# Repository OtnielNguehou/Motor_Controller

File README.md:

# Motor_Controller
Designed and developed a custom PCB-based voltage multiplier circuit to generate a higher DC output voltage from a low-voltage input source. The project was motivated by the need to provide sufficient voltage for a future DC motor controller design while utilizing readily available components.

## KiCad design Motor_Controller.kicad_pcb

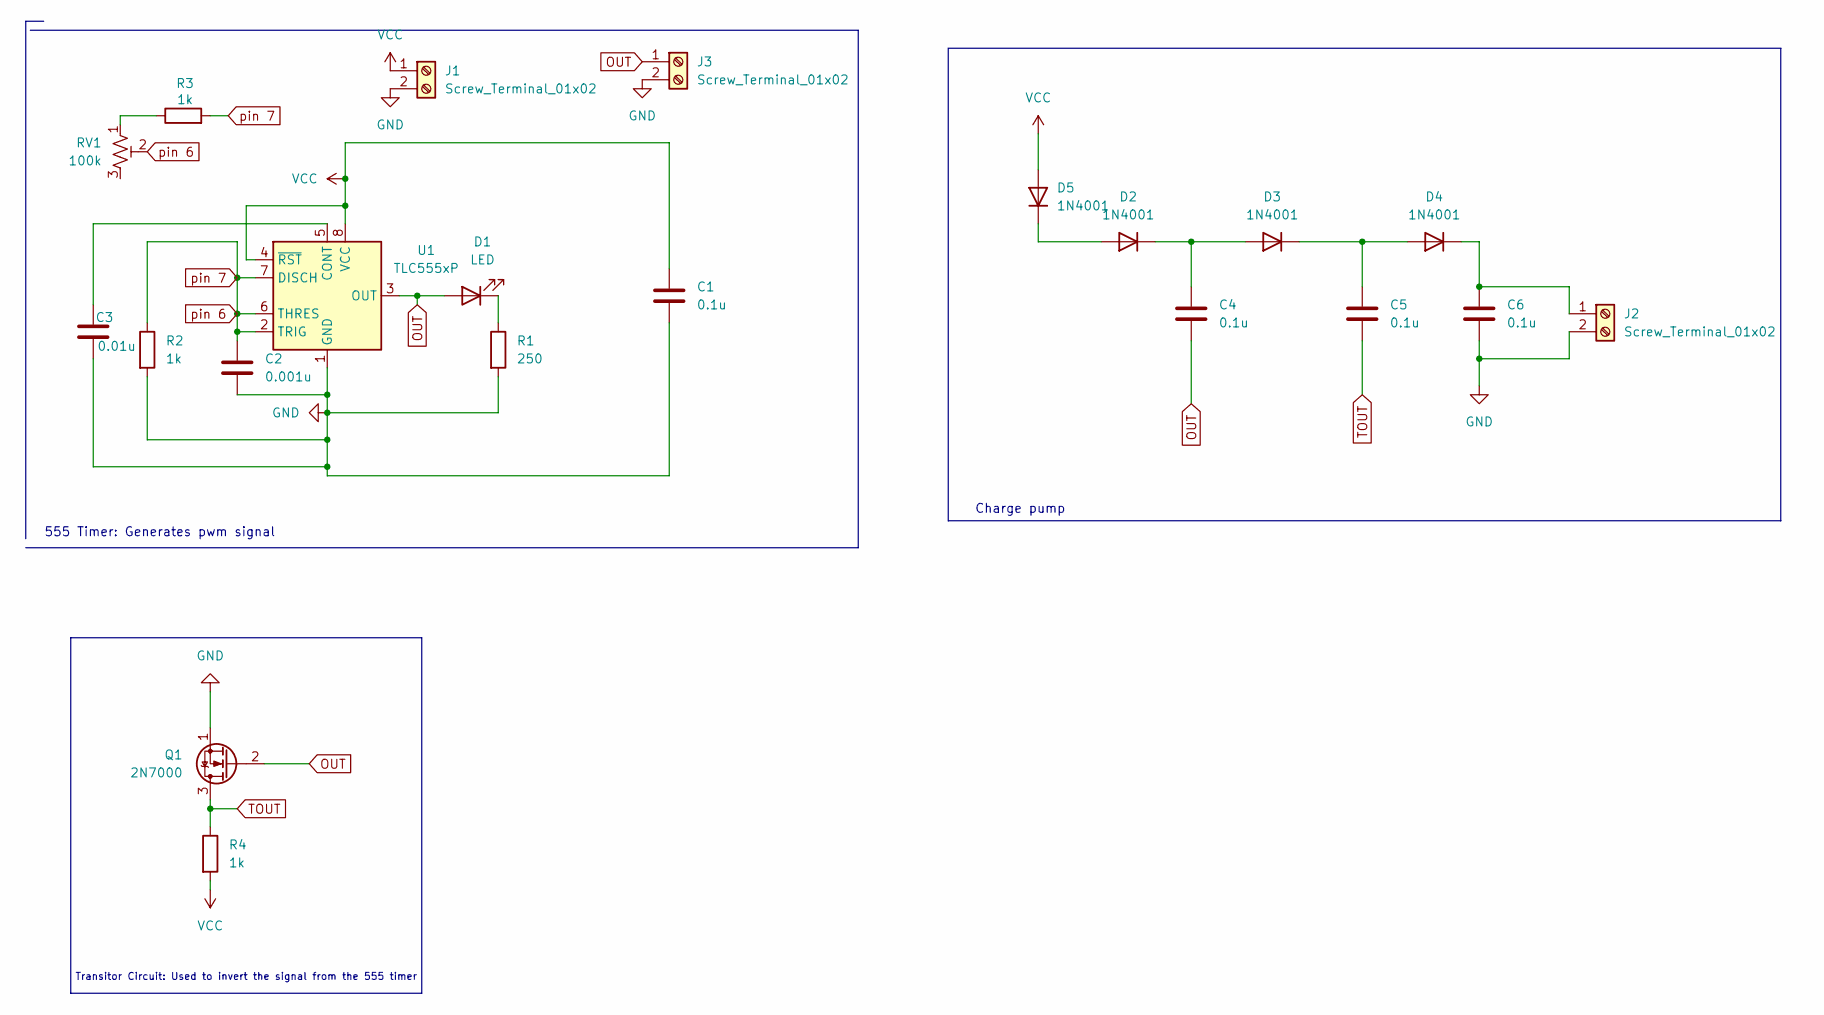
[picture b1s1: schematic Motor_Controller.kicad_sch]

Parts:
C1, C4, C5, C6: 0.1u; C_Rect_L4.6mm_W2.0mm_P2.50mm_MKS02_FKP02
C2: 0.001u; C_Rect_L4.6mm_W2.0mm_P2.50mm_MKS02_FKP02
C3: 0.01u; C_Rect_L4.6mm_W2.0mm_P2.50mm_MKS02_FKP02
D1: LED; LED_D3.0mm_Horizontal_O1.27mm_Z2.0mm
D2, D3, D4, D5: 1N4001; D_DO-41_SOD81_P10.16mm_Horizontal
J1, J2, J3: Screw_Terminal_01x02; TerminalBlock_Xinya_XY308-2.54-2P_1x02_P2.54mm_Horizontal
Q1: 2N7000; TO-92_Inline
R1: 250; R_Axial_DIN0204_L3.6mm_D1.6mm_P5.08mm_Horizontal
R2, R3, R4: 1k; R_Axial_DIN0204_L3.6mm_D1.6mm_P5.08mm_Horizontal
RV1: 100k; Potentiometer_Vishay_T93YA_Vertical
U1: TLC555xP; DIP-8_W7.62mm

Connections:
GND: C1.2, C2.2, C3.2, C6.2, J1.2, J2.2, J3.2, Q1.1 (S), R1.2, R2.2, U1.1 (GND)
unnamed: D1.1 (K), R1.1
unnamed: D2.2 (A), D5.1 (K)
unnamed: C4.1, D2.1 (K), D3.2 (A)
unnamed: C5.1, D3.1 (K), D4.2 (A)
unnamed: C6.1, D4.1 (K), J2.1
unnamed: R3.1, RV1.1
unnamed: C3.1, U1.5 (CONT)
OUT: C4.2, D1.2 (A), J3.1, Q1.2 (G), U1.3 (OUT)
TOUT: C5.2, Q1.3 (D), R4.1
VCC: C1.1, D5.2 (A), J1.1, R4.2, U1.4 (~RST), U1.8 (VCC)
pin 6: C2.1, R2.1, R3.2, RV1.2, U1.2 (TRIG), U1.6 (THRES), U1.7 (DISCH)

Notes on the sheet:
Charge pump
Transitor Circuit: Used to invert the signal from the 555 timer
555 Timer: Generates pwm signal

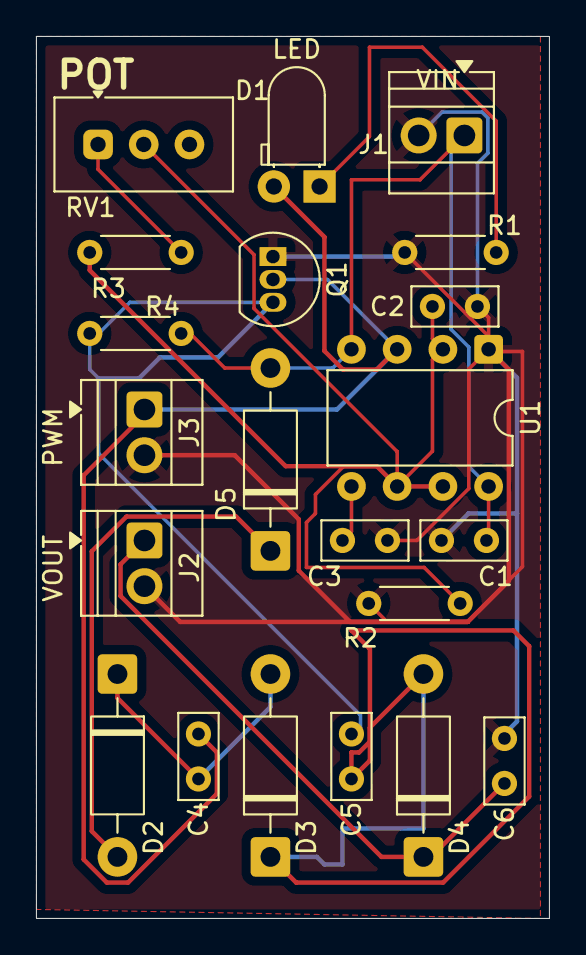
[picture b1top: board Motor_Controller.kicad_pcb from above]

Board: 2 copper layers, 28.5 x 49.0 mm, 21 parts (0 on the bottom side), 12 nets.

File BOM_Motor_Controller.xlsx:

Reference | Qty | Value | DNP | Exclude from BOM | Exclude from Board | Footprint | Datasheet
C1,C4 | 2 | 0.1u |  |  |  | Capacitor_THT:C_Rect_L4.6mm_W2.0mm_P2.50mm_MKS02_FKP02 | ~
C2 | 1 | 0.001u |  |  |  | Capacitor_THT:C_Rect_L4.6mm_W2.0mm_P2.50mm_MKS02_FKP02 | ~
C3 | 1 | 0.01u |  |  |  | Capacitor_THT:C_Rect_L4.6mm_W2.0mm_P2.50mm_MKS02_FKP02 | ~
C5 | 1 | 01u |  |  |  | Capacitor_THT:C_Rect_L4.6mm_W2.0mm_P2.50mm_MKS02_FKP02 | ~
C6 | 1 | 01u |  |  |  | Capacitor_THT:C_Radial_D6.3mm_H5.0mm_P2.50mm | ~
D1 | 1 | LED |  |  |  | LED_THT:LED_D3.0mm_Horizontal_O1.27mm_Z2.0mm | ~
D2,D3,D4,D5 | 4 | 1N4001 |  |  |  | Diode_THT:D_DO-41_SOD81_P10.16mm_Horizontal | http://www.vishay.com/docs/88503/1n4001.pdf
Q1 | 1 | 2N7000 |  |  |  | Package_TO_SOT_THT:TO-92_Inline | https://www.vishay.com/docs/70226/70226.pdf
R1 | 1 | 250 |  |  |  | Resistor_THT:R_Axial_DIN0204_L3.6mm_D1.6mm_P5.08mm_Horizontal | ~
R2,R3,R4 | 3 | 1k |  |  |  | Resistor_THT:R_Axial_DIN0204_L3.6mm_D1.6mm_P5.08mm_Horizontal | ~
RV1 | 1 | 100k |  |  |  | Potentiometer_THT:Potentiometer_Alps_RK09Y11_Single_Horizontal | ~
U1 | 1 | TLC555xP |  |  |  | Package_DIP:DIP-8_W7.62mm | http://www.ti.com/lit/ds/symlink/tlc555.pdf
